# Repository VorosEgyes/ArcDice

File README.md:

# ArcDice

ArcDice is a compact ATtiny13-based digital dice project with a 7-LED face, low-power sleep behavior, and a matching KiCad hardware design.

Keywords: digital dice, ATtiny13 dice, LED dice, DIY electronic dice.

## What It Does

- Rolls a random value from 1 to 6 with a short LED animation.
- Drives a 7-point dice face from only 4 MCU output lines.
- Uses button wake-up and sleep mode to reduce power draw.

## Firmware

- Source: `src/main.cpp`
- PlatformIO environment: `attiny13a`
- Upload protocol: `usbasp`

### Pin Mapping

- PB0 -> center LED segment
- PB1 -> diagonal A (top-left + bottom-right)
- PB2 -> diagonal B (top-right + bottom-left)
- PB3 -> middle row (left-middle + right-middle)
- PB4 -> roll button (to GND, internal pull-up)

### Dice Face Layout

The 7 visible pips are arranged on a 3x3 grid and lit via 4 logical
groups (center, two diagonals, middle row). The resulting faces are:

| Roll | Pattern                       | Description           |
|------|-------------------------------|-----------------------|
| 1    | center                        | single center pip     |
| 2    | diagonal A                    | two corner pips (TL+BR) |
| 3    | center + diagonal A           | vertical middle column (TL + center + BR) |
| 4    | diagonal A + diagonal B       | four corners (full X) |
| 5    | center + both diagonals       | full X plus center    |
| 6    | both diagonals + middle row   | four corners + middle two |

Note: face 3 uses diagonal A (TL+BR) plus center, giving a symmetric
vertical middle column -- the standard 7-pip rendering of 3.

## Hardware

- KiCad project files:
	- `hardware/ArcDice.kicad_pro`
	- `hardware/ArcDice.kicad_sch`
	- `hardware/ArcDice.kicad_pcb`
- Power target: 1S Li-ion/LiPo with TP4056 protected module
- Recommended LED resistors: 220 ohm (one per LED)

## Images

### Assembled Board

### Bare PCB

### 3D Top

### 3D Bottom

### Schematic v1

## Build And Upload

1. Install PlatformIO.
2. Connect an ATtiny13 programmer (USBasp).
3. Build and upload:

```bash
pio run -e attiny13a -t upload
```

## Additional Documentation

- [CHANGELOG.md](CHANGELOG.md) — release history and notable changes.
- [docs/BOM.md](docs/BOM.md) — bill of materials with footprints and suggested supplier parts.

## License

MIT. See `LICENSE`.

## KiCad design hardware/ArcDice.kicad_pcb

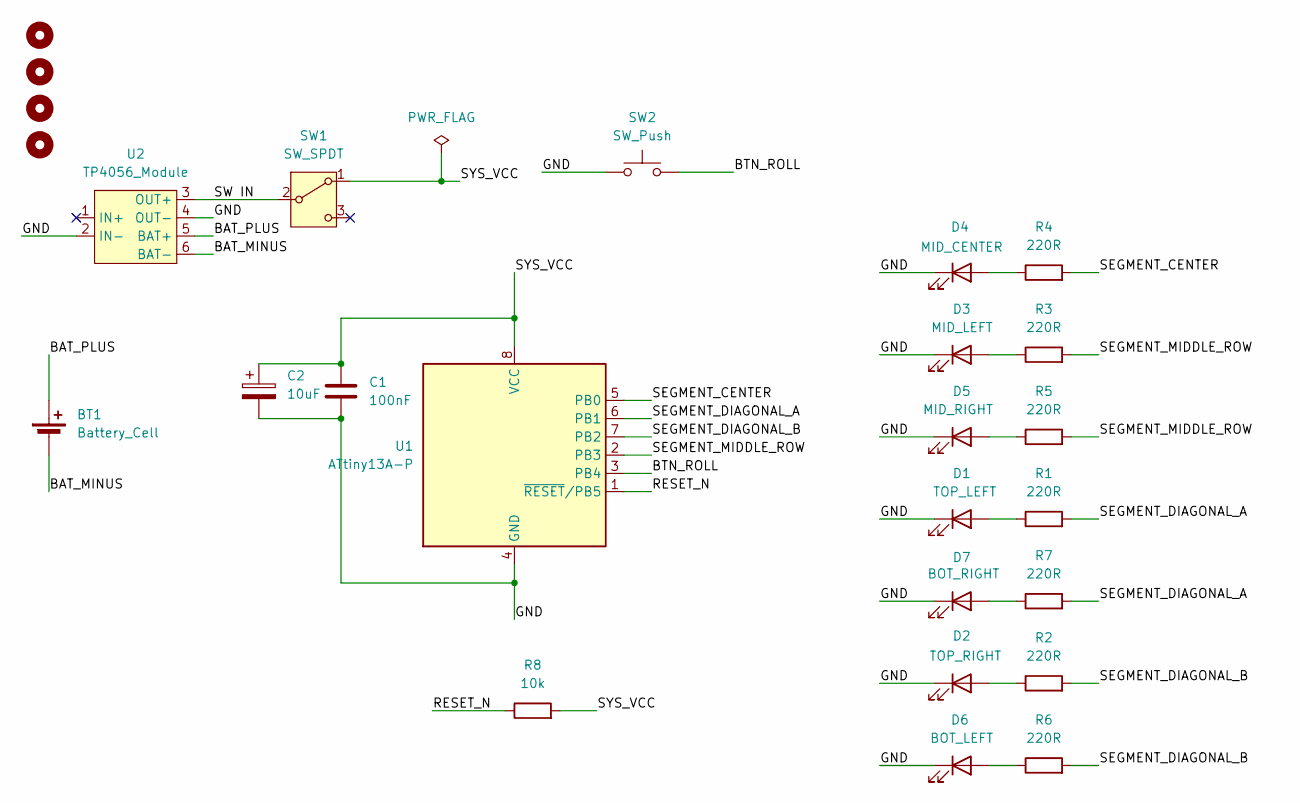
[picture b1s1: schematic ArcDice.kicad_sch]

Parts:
BT1: Battery_Cell; Battery_18250_Tabbed_1S
C1: 100nF; C_Disc_D3.0mm_W1.6mm_P2.50mm
C2: 10uF; CP_Radial_D5.0mm_P2.00mm
D1, D2, D3, D4, D5, D6, D7: LED; LED_D5.0mm
H1, H2, H3, H4: MountingHole; MountingHole_3.2mm_M3
R1, R2, R3, R4, R5, R6, R7: 220R; R_Axial_DIN0207_L6.3mm_D2.5mm_P7.62mm_Horizontal
R8: 10k; R_Axial_DIN0207_L6.3mm_D2.5mm_P7.62mm_Horizontal
SW1: SW_SPDT; Switch_Slide_SS12D06_Generic
SW2: SW_Push; SW_PUSH_6mm_H9.5mm
U1: ATtiny13A-P; DIP-8_W7.62mm
U2: TP4056_Module; TP4056-Module

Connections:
/BAT_MINUS: BT1.2 (-), U2.6 (BAT-)
/BAT_PLUS: BT1.1 (+), U2.5 (BAT+)
/BTN_ROLL: SW2.2, U1.3 (PB4)
/GND: C1.2, C2.2, D1.1 (K), D2.1 (K), D3.1 (K), D4.1 (K), D5.1 (K), D6.1 (K), D7.1 (K), SW2.1, U1.4 (GND), U2.2 (IN-), U2.4 (OUT-)
/RESET_N: R8.1, U1.1 (~RESET/PB5)
/SEGMENT_CENTER: R4.2, U1.5 (PB0)
/SEGMENT_DIAGONAL_A: R1.2, R7.2, U1.6 (PB1)
/SEGMENT_DIAGONAL_B: R2.2, R6.2, U1.7 (PB2)
/SEGMENT_MIDDLE_ROW: R3.2, R5.2, U1.2 (PB3)
/SW IN: SW1.2 (B), U2.3 (OUT+)
/SYS_VCC: C1.1, C2.1, R8.2, SW1.1 (A), U1.8 (VCC)
unnamed: D1.2 (A), R1.1
unnamed: D2.2 (A), R2.1
unnamed: D3.2 (A), R3.1
unnamed: D4.2 (A), R4.1
unnamed: D5.2 (A), R5.1
unnamed: D6.2 (A), R6.1
unnamed: D7.2 (A), R7.1

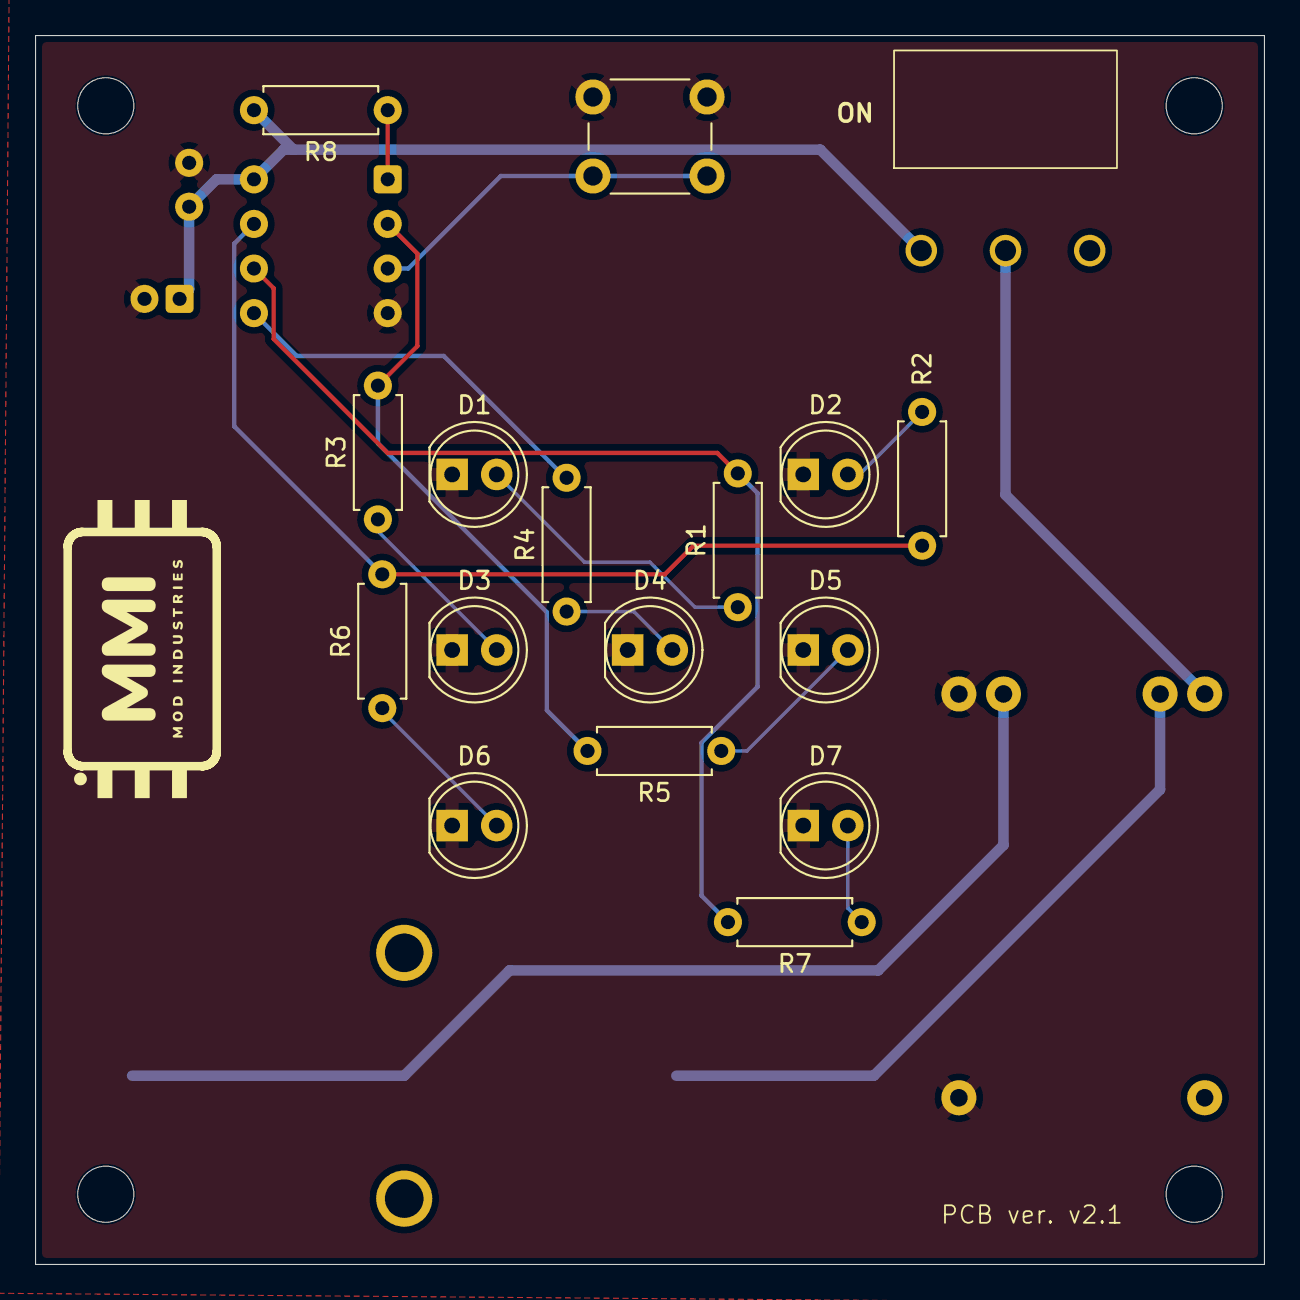
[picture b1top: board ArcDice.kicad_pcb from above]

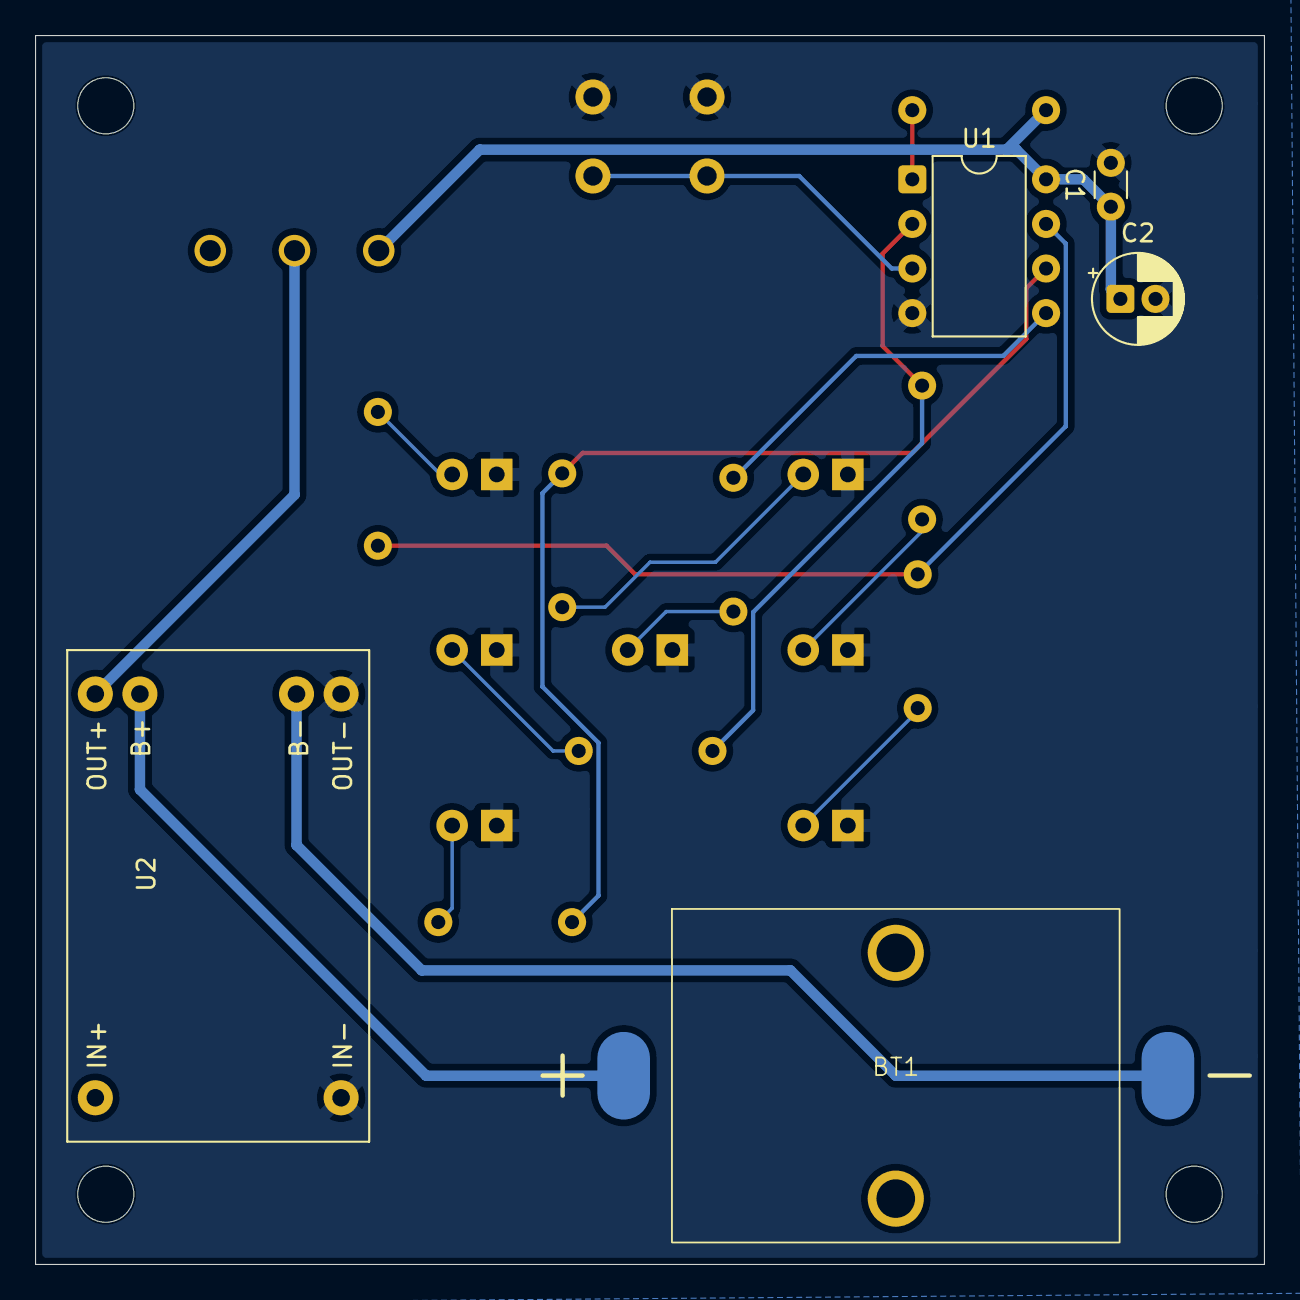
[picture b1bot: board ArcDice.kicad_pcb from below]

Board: 2 copper layers, 70.0 x 70.0 mm, 26 parts (5 on the bottom side), 18 nets.

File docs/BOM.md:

# Bill of Materials (BOM)

This document lists every component needed to build one ArcDice unit.
It is derived from the KiCad project (`hardware/ArcDice.kicad_pro`,
`.kicad_sch`, `.kicad_pcb`) and the firmware pin mapping in
`src/main.cpp`. Footprints are taken straight from the KiCad library
references.

> **Sourcing note** — KiCad footprints identify the *physical package*
> (e.g. `LED_D5.0mm`, `R_Axial_DIN0207`). For exact distributor part numbers
> (Digi-Key, Mouser, LCSC), see the *Suggested supplier parts* column. Any
> equivalent part that matches footprint and electrical specs will work.

## Components

| Ref | Qty | Part (KiCad) | Description | Footprint / package | Suggested supplier part |
|----:|----:|--------------|-------------|---------------------|--------------------------|
| U1 | 1 | `ATtiny13A-P` | 8-bit AVR MCU, 1 KB flash, 64 B EEPROM, 64 B SRAM, internal 9.6 MHz oscillator | DIP-8 (through-hole) | Microchip ATtiny13A-PU (Digi-Key ATATTINY13A-PU-ND) |
| D1–D7 | 7 | `LED` (generic) | 5 mm through-hole LED — pick your colour (red, yellow, green, blue, white all fit). Forward voltage ~2.0 V (red) to ~3.2 V (blue/white) at 20 mA | `LED_THT:LED_D5.0mm` | Kingbright L-7113ID (red, THT, 5 mm) or any 5 mm LED of your choice |
| R1–R7 | 7 | Resistor 220 Ω, ¼ W | LED current-limiting. With 3.0 V Li-ion and a red LED (~2 V Vf), 220 Ω gives ~5 mA per LED — plenty for a battery-powered dice | `Resistor_THT:R_Axial_DIN0207_L6.3mm_D2.5mm_P7.62mm_Horizontal` | Yageo MFR-25FBF52-220R (Digi-Key 220XBK-ND) |
| SW1 | 1 | `SW_Push` — roll button | 6 mm × 9.5 mm through-hole tactile push button, SPST-NO. Connected to PB4 to GND, internal pull-up enabled in firmware | `Button_Switch_THT:SW_PUSH_6mm_H9.5mm` | C&K PTS810SJM250SMTRLFS or any equivalent 6 mm THT tactile |
| SW2 | 1 | `Switch_Slide_SS12D06_Generic` | SPDT slide switch — most likely the power on/off switch between battery and TP4056 / load | `Button_Switch_THT:Switch_Slide_SS12D06_Generic` | SS12D06G3 or any equivalent SPDT slide switch, THT |
| SW3 | 1 | `SW_SPDT` | Second SPDT switch — check schematic for exact use (likely mode-select or reset disable) | (KiCad symbol `Switch:SW_SPDT`, footprint TBD) | Any SPDT THT slide/toggle switch |
| BT1 | 1 | `Battery_Cell` | Single 3.7 V Li-ion / LiPo cell (1S), nominal capacity 100–500 mAh typical for a dice. Use a protected cell (with BMS) and add a 1N4148 flyback diode if driving the LEDs without other regulation | Through-hole battery holder footprint (KiCad `Device:Battery_Cell`) | 1S Li-ion/LiPo |
| U2 | 1 | `TP4056_Module` | TP4056 Li-ion/LiPo linear charging module, micro-USB or USB-C input depending on the module variant. Charges the cell from any 5 V source; module typically includes a DW01 + FS8205 protection IC. Note: the **module** is mounted, not the bare TP4056 IC | Through-hole 4-pin module (OUT+/OUT−/IN+/IN−) | TP4056 micro-USB module (LCSC C103626) or USB-C variant (LCSC C2932096) |
| C1, C2 | 2 | Decoupling capacitors | Polarized + unpolarized decoupling. Typical: 100 nF ceramic (unpolarized) on ATtiny AVCC, and 10 µF electrolytic (polarized) across battery / TP4056 output for smooth LED current | THT, 5 mm pitch (KiCad `Device:C` and `Device:CP`) | Murata RDER71H104K (100 nF) + Nichicon UPW1A100MDD (10 µF) |
| H1–H4 | 4 | M2 mounting holes, 2.2 mm drill | Mechanical mounting only — use with M2 × 4 (or longer) pan-head screws and (optional) 4 mm hex spacers | `MountingHole:MountingHole_2.2mm_M2` | M2 × 4 pan-head screw + M2 hex spacer, 4 each |

## Component count summary

- **Active:** 1 MCU + 1 charger module = **2**
- **Passive:** 7 resistors + 2 capacitors = **9**
- **LEDs:** 7
- **Switches:** 3 (1 push button + 2 SPDT slide switches)
- **Battery:** 1 cell (1S Li-ion/LiPo, user-supplied, not part of a bare kit)
- **Mechanical:** 4 M2 mounting holes

## What is NOT on this BOM

- **USBasp programmer** — required to flash the ATtiny13A initially, but not part of the assembled board.

- **Battery** — listed above for reference but typically user-supplied (a protected 1S cell with leads).
- **Enclosure / 3D-printed case** — not in the current hardware design.

## Notes for sourcing

1. **LED colour** — pick whatever you prefer; the firmware doesn't depend on it. If you mix colours, double-check the forward voltage: a 220 Ω resistor is fine for red/yellow/green (~2 V Vf). For blue/white (~3 V Vf) you'll want closer to 100 Ω to keep the LED brightness matched at ~5–10 mA.
2. **Resistor power rating** — 220 Ω × 5 mA = ~5.5 mW per resistor, so ¼ W is enormous overkill; even 1/8 W works.
3. **TP4056 module vs. bare IC** — the BOM uses the *module*, not the bare TP4056 IC, because the module integrates the DW01 + FS8205 protection and the micro-USB connector. If you want to redesign around the bare IC (smaller PCB, no on-board USB), that is a v2 hardware decision, not a BOM change.
4. **Battery polarity** — make sure your 1S cell has a protection circuit (BMS). The TP4056 module by itself does not include over-discharge protection.

## Sourcing shortcuts

| Supplier | Region | Best for |
|----------|--------|----------|
| LCSC | China / EU warehouse | TP4056 module, basic passives, LEDs |
| Digi-Key | Worldwide | ATtiny13A-PU (genuine Microchip), quality passives |
| Mouser | Worldwide | Same as Digi-Key, often better for European orders |
| TME | EU (Hungary-friendly) | Through-hole resistors, capacitors, LEDs, switches |
| Reichelt | DE / EU | German warehouse, good for DIN0207 resistors |
| AliExpress | China | Cheapest TP4056 modules and LEDs, expect 2–4 week shipping |

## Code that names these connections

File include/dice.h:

// dice.h — Pure-logic header for the dice face mapping.
//
// This file is intentionally free of Arduino-specific includes so it can
// be compiled both by the ATtiny13A firmware and by the host-native test
// runner (PlatformIO `pio test -e native`).
//
// The hardware layout (PB0..PB3 as display segments, PB4 as the button)
// is fixed in stone at the schematic level — see docs/BOM.md and the
// main README. Changing these values here without changing the firmware
// pin mapping AND the KiCad schematic will produce a board that lights
// up the wrong segments.

#ifndef ARCDICE_DICE_H_
#define ARCDICE_DICE_H_

#include <stdint.h>

// Bit positions on ATtiny13A PORTB. Keep in sync with src/main.cpp.
#ifndef DICE_SEGMENT_CENTER
#define DICE_SEGMENT_CENTER     0   // PB0 — center pip (CC)
#endif
#ifndef DICE_SEGMENT_DIAGONAL_A
#define DICE_SEGMENT_DIAGONAL_A 1   // PB1 — TL + BR diagonal
#endif
#ifndef DICE_SEGMENT_DIAGONAL_B
#define DICE_SEGMENT_DIAGONAL_B 2   // PB2 — TR + BL diagonal
#endif
#ifndef DICE_SEGMENT_MIDDLE_ROW
#define DICE_SEGMENT_MIDDLE_ROW 3   // PB3 — ML + MR middle row
#endif

#define DICE_BUTTON_PIN         4   // PB4 — roll button input

#define DICE_BIT(bit)           ((uint8_t)(1u << (bit)))

namespace arcdice {

constexpr uint8_t kCenterMask     = DICE_BIT(DICE_SEGMENT_CENTER);
constexpr uint8_t kDiagonalAMask  = DICE_BIT(DICE_SEGMENT_DIAGONAL_A);
constexpr uint8_t kDiagonalBMask  = DICE_BIT(DICE_SEGMENT_DIAGONAL_B);
constexpr uint8_t kMiddleRowMask  = DICE_BIT(DICE_SEGMENT_MIDDLE_ROW);

constexpr uint8_t kButtonMask     = DICE_BIT(DICE_BUTTON_PIN);

constexpr uint8_t kDisplayMask =
    kCenterMask | kDiagonalAMask | kDiagonalBMask | kMiddleRowMask;

// Face indices are 0..6 inclusive. Face 0 is the "all off" sentinel
// (never displayed by the firmware — roll() returns 1..6) but is included
// here so the array length matches the README's 1..6 documentation.
//
// The mapping matches the README "Dice Face Layout" table:
//
//   face 1 = center
//   face 2 = diagonal A
//   face 3 = center + diagonal A           (vertical middle column)
//   face 4 = diagonal A + diagonal B       (full X, four corners)
//   face 5 = center + diagonals A + B      (full X + center)
//   face 6 = diagonals A + B + middle row  (four corners + middle two)
constexpr uint8_t kDiceFaceMasks[7] = {
    0,                                              // face 0 — unused
    kCenterMask,                                    // face 1
    kDiagonalAMask,                                  // face 2
    kCenterMask | kDiagonalAMask,                    // face 3
    kDiagonalAMask | kDiagonalBMask,                 // face 4
    kCenterMask | kDiagonalAMask | kDiagonalBMask,   // face 5
    kDiagonalAMask | kDiagonalBMask | kMiddleRowMask, // face 6
};

// Returns the PORTB mask for the requested face. Faces 1..6 are valid;
// face 0 returns 0 (all segments off). Out-of-range faces return 0xFF
// so a programming error is visible immediately rather than silently
// rolling "all off".
constexpr uint8_t faceMask(uint8_t face) {
    return (face < 7) ? kDiceFaceMasks[face] : 0xFF;
}

}  // namespace arcdice

#endif  // ARCDICE_DICE_H_
